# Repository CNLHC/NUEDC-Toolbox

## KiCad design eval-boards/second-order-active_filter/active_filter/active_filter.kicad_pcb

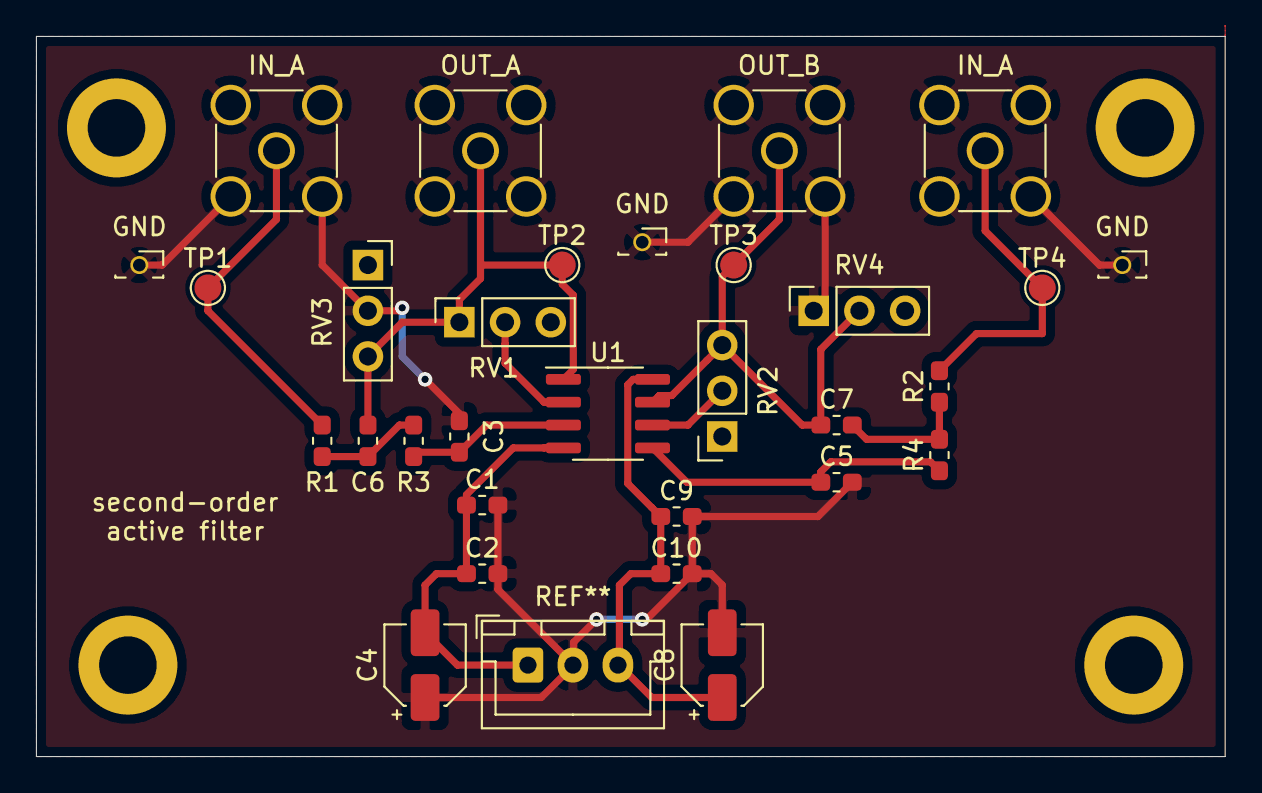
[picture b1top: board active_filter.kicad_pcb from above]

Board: 2 copper layers, 66.0 x 40.0 mm, 30 parts (0 on the bottom side), 13 nets.

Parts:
C1, C2: 0.1uf; C_0603_1608Metric_Pad1.05x0.95mm_HandSolder
C3, C5, C6, C7: C; C_0603_1608Metric_Pad1.05x0.95mm_HandSolder
C4, C8: 10uF; CP_Elec_4x5.3
C9, C10: 0.1uF; C_0603_1608Metric_Pad1.05x0.95mm_HandSolder
GND: PinSocket_1x01_P1.27mm_Vertical
GND#2, GND#3: PinSocket_1x01_P1.27mm_Vertical
IN_A: IN_A; SMA_Amphenol_132134-11_Vertical
IN_A#2: IN_B; SMA_Amphenol_132134-11_Vertical
OUT_A: OUT_A; SMA_Amphenol_132134-11_Vertical
OUT_B: OUT_B; SMA_Amphenol_132134-11_Vertical
R1, R2, R3, R4: R; R_0603_1608Metric_Pad1.05x0.95mm_HandSolder
RV1, RV2, RV3, RV4: PinSocket_1x03_P2.54mm_Vertical
TP1, TP2, TP3, TP4: TestPoint_Pad_D1.5mm
U1: ADA4075-2; SOIC-8_3.9x4.9mm_P1.27mm

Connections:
/VCC: C8.1, C9.1, C10.1, U1.8
/VEE: C1.1, C2.1, C4.2, U1.4
GND: C1.2, C2.2, C3.2, C4.1, C5.2, C8.2, C9.2, C10.2, GND.1, GND#2.1, GND#3.1, IN_A.2, IN_A#2.2, OUT_A.2, OUT_B.2, RV3.2, RV4.1
unnamed: C3.1, R3.1, U1.3
unnamed: C5.1, R4.1, U1.5
unnamed: C6.1, OUT_A.1, RV1.1, RV3.3, TP2.1, U1.1
unnamed: C6.2, R1.1, R3.2
unnamed: C7.1, OUT_B.1, RV2.3, RV4.2, TP3.1, U1.7
unnamed: C7.2, R2.1, R4.2
unnamed: IN_A.1, R1.2, TP1.1
unnamed: IN_A#2.1, R2.2, TP4.1
unnamed: RV1.2, U1.2
unnamed: RV2.2, U1.6

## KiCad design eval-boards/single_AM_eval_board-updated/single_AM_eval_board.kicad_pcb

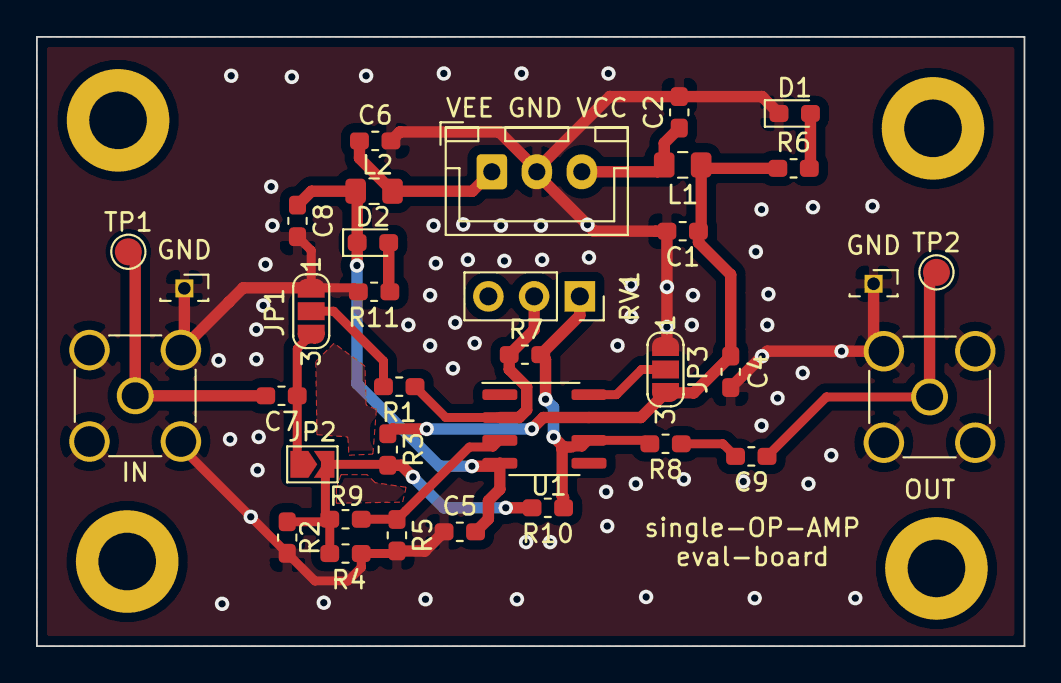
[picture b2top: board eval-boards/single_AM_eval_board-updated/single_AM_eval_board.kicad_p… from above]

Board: 2 copper layers, 54.9 x 33.8 mm, 35 parts (0 on the bottom side), 17 nets.

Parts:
C1, C2, C6, C8: 10uF; C_0603_1608Metric_Pad1.05x0.95mm_HandSolder
C4, C5: 100nF; C_0603_1608Metric_Pad1.05x0.95mm_HandSolder
C7, C9: C; C_0603_1608Metric_Pad1.05x0.95mm_HandSolder
D1, D2: LED_ALT; LED_0603_1608Metric_Pad1.05x0.95mm_HandSolder
GND: PinSocket_1x01_P1.27mm_Vertical
GND#2: PinSocket_1x01_P1.27mm_Vertical
IN: Conn_Coaxial; SMA_Amphenol_132134-11_Vertical
JP1, JP3: Jumper_3_Open; SolderJumper-3_P1.3mm_Open_RoundedPad1.0x1.5mm_NumberLabels
JP2: Jumper_2_Open; SolderJumper-2_P1.3mm_Open_TrianglePad1.0x1.5mm
L1, L2: L_Core_Iron; L_0805_2012Metric_Pad1.15x1.40mm_HandSolder
OUT: Conn_Coaxial; SMA_Amphenol_132134-11_Vertical
R1, R2, R3, R4, R5, R7, R8, R9, R10: R; R_0603_1608Metric_Pad1.05x0.95mm_HandSolder
R6, R11: 1K; R_0603_1608Metric_Pad1.05x0.95mm_HandSolder
RV1: R_POT; PinSocket_1x03_P2.54mm_Vertical
TP1, TP2: TestPoint_Pad_D1.5mm
U1: ADA4522-1; SOIC-8_3.9x4.9mm_P1.27mm
VEE GND VCC: Conn_01x03_Male; JST_XH_B3B-XH-A_1x03_P2.50mm_Vertical

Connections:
/VCC: C1.1, C4.2, JP3.3, L1.1, R3.1, R6.1, U1.7
/VEE: C5.2, C8.1, D2.1, L2.2, U1.4
GND: C1.2, C2.2, C4.1, C5.1, C6.2, C8.2, D1.1, GND.1, GND#2.1, IN.2, JP1.1, JP3.1, OUT.2, R2.2, R4.2, R5.2, R11.2, VEE GND VCC.2
unnamed: C2.1, L1.2, VEE GND VCC.3
unnamed: C6.1, L2.1, VEE GND VCC.1
unnamed: C7.1, JP1.3, JP2.1
unnamed: C7.2, IN.1, TP1.1
unnamed: C9.1, OUT.1, TP2.1
unnamed: C9.2, R8.1
unnamed: D1.2, R6.2
unnamed: D2.2, R11.1
unnamed: JP1.2, R1.2
unnamed: JP2.2, R2.1, R3.2, R4.1, R9.2, R10.2
unnamed: JP3.2, U1.8
unnamed: R1.1, R7.2, RV1.2, U1.2
unnamed: R5.1, R9.1, U1.3
unnamed: R7.1, R8.2, R10.1, RV1.1, U1.6

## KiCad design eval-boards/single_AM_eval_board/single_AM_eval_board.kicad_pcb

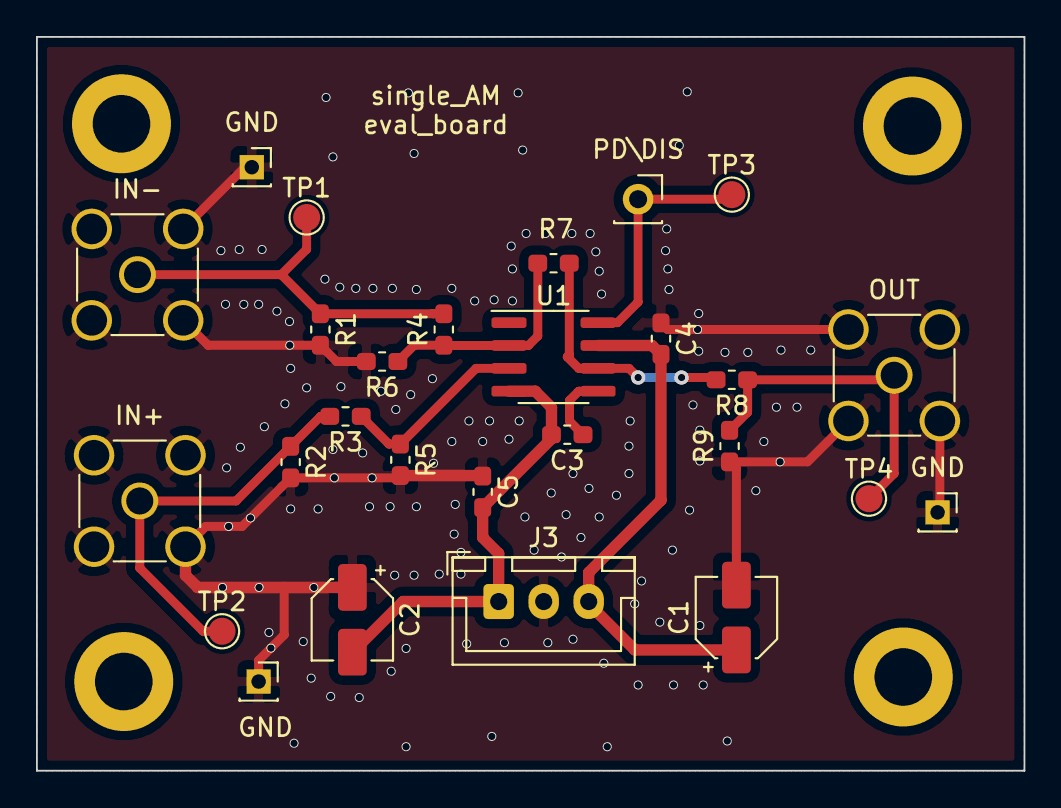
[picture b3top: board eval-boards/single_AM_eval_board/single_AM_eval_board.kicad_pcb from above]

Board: 2 copper layers, 54.9 x 40.8 mm, 27 parts (0 on the bottom side), 11 nets.

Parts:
C1, C2: 10uF; CP_Elec_4x5.4
C3, C4, C5: C; C_0603_1608Metric_Pad1.05x0.95mm_HandSolder
GND: PinSocket_1x01_P2.00mm_Vertical
GND#2, GND#3: PinSocket_1x01_P2.00mm_Vertical
IN+: Conn_Coaxial; SMA_Amphenol_132134-11_Vertical
IN-: Conn_Coaxial; SMA_Amphenol_132134-11_Vertical
J3: Conn_01x03_Male; JST_XH_B3B-XH-A_1x03_P2.50mm_Vertical
OUT: Conn_Coaxial; SMA_Amphenol_132134-11_Vertical
PD\DIS: Conn_01x01_Male; PinSocket_1x01_P2.54mm_Vertical
R1, R2, R3, R4, R5, R6, R7, R8, R9: R; R_0603_1608Metric_Pad1.05x0.95mm_HandSolder
TP1, TP3, TP4: TestPoint; TestPoint_Pad_D1.5mm
TP2: TestPoint_Pad_D1.5mm
U1: ADA4522-1; SOIC-8_3.9x4.9mm_P1.27mm

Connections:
/VCC: C1.1, C4.2, J3.3, U1.7
/VEE: C2.2, C3.2, C5.2, J3.1, U1.4
GND: C1.2, C2.1, C4.1, C5.1, GND.1, GND#2.1, GND#3.1, IN+.2, IN-.2, J3.2, OUT.2, R1.2, R2.2, R5.2, R6.2, R9.1
unnamed: C3.1, U1.5
unnamed: IN-.1, R1.1, R4.2, TP1.1
unnamed: IN+.1, R2.1, R3.2, TP2.1
unnamed: OUT.1, R8.1, R9.2, TP4.1
unnamed: PD\DIS.1, TP3.1, U1.8
unnamed: R3.1, R5.1, U1.3
unnamed: R4.1, R6.1, R7.2, U1.2
unnamed: R7.1, R8.2, U1.6
